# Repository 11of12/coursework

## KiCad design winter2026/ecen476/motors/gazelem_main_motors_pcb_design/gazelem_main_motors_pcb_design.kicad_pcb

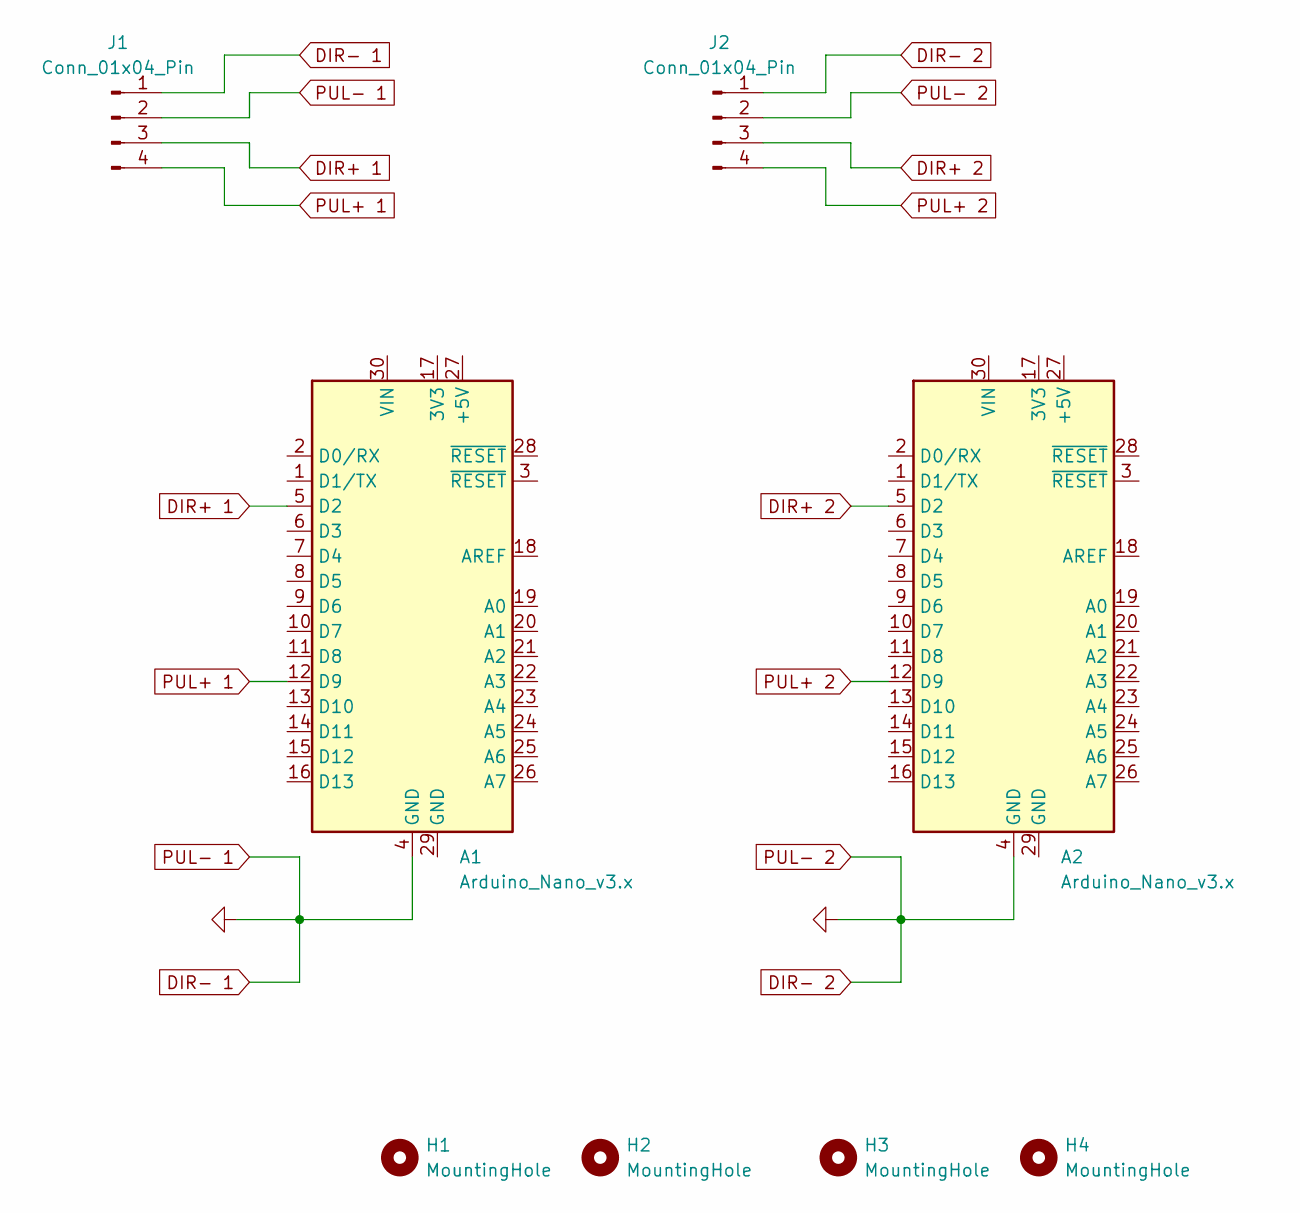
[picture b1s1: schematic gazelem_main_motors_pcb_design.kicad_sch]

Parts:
A1, A2: Arduino_Nano_v3.x; Arduino_Nano_WithMountingHoles
H1, H2, H3, H4: MountingHole; MountingHole_2.1mm
J1, J2: Conn_01x04_Pin; PinHeader_1x04_P2.00mm_Horizontal

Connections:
DIR+ 1: A1.5 (D2), J1.3
DIR+ 2: A2.5 (D2), J2.3
DIR- 1: A1.4 (GND), A2.4 (GND), J1.1, J1.2, J2.1, J2.2
PUL+ 1: A1.12 (D9), J1.4
PUL+ 2: A2.12 (D9), J2.4

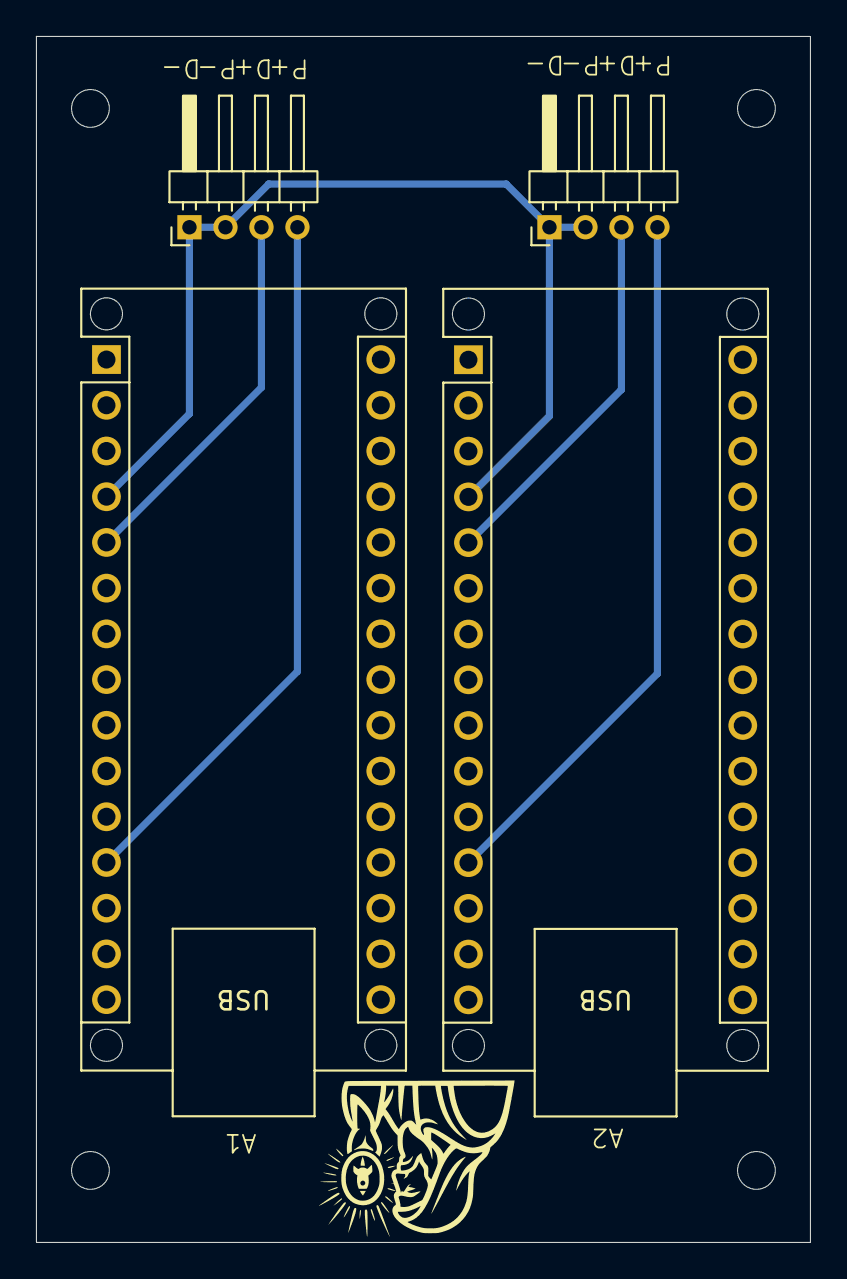
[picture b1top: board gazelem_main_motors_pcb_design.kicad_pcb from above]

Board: 2 copper layers, 43.0 x 67.0 mm, 8 parts (0 on the bottom side), 5 nets.

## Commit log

2026-02-16 Commit from Aspire
2026-02-17 Fixed naming conventions
2026-02-17 added gitignore
2026-02-17 Apparently I didn't add things before
2026-02-17 Succesfully added 471 code
2026-02-17 hold on
2026-02-17 fixed the submodule issue
2026-02-17 Added code for arduino programming
2026-02-18 Completed code for ecen471 project 2
2026-02-18 Added ecen555 code so far
2026-02-19 Started pcb for main motors
2026-02-21 Finished pcb and added code for 471 hw5
2026-02-21 Might as well
2026-02-25 Finished 471 hw 5
2026-03-14 Completed 555 hw 5
2026-03-14 added gitignore in 555
2026-03-14 Stopped tracking the book
2026-03-14 changed the file name
2026-03-14 added conclusion to prob 3.23
2026-03-26 Finsished project 3 471
2026-03-28 Implented logistic regression and gradient descent for homework 6
2026-04-01 Finsihed hw6 ecen471
2026-04-01 Finished most of the problems in Ecen555 HW6
2026-04-04 Began final homework for 555 and 471
2026-04-04 Finished ECEN471 HW7
2026-04-05 Created First Attempt at Neural Network
2026-04-05 Kept working
2026-04-09 Finished first 2 555 problems on HW7
2026-04-11 Finished first draft of ECEN555 HW7
